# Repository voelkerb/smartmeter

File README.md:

# SmartMeter

The SmartMeter is a WiFi and Ethernet equipped electricity meter that to be installed in a home's fuse box. 
The development started with hardware [Version 1.0](/Schematic/Version_1). It consists of an ESP32 microcontroller and a dedicated electricity monitoring chip. As the main idea behind this project was to record voltage and current waveforms at higher frequencies, several drawbacks for this use case were fixed with Hardware [Version 2.0](/Schematic/Version_2). It features the same Microcontroller but with 8MB internal storage for data buffering, an RTC for precise time keeping while sampling, a faster USB serial connection with up to 12Mbaud and a 100Mbit ethernet interface.

If you are just interested in the consumption of a single appliance, see the [PowerMeter](https://github.com/voelkerb/powermeter) instead.

## Why to use?
It's open source, easy to use, easy to build and offers lots of flexibility. 

The hardware is...
* tested to work reliable with 230V.
* rather cheap (all components sum up to around 70€).

The firmware supports...
* existing 2.4GHz WPA2 networks or can create its own network.
* to receive commands via USB, TCP or MQTT.
* to store the configuration in the internal non volatile memory.
* to provide data at sampling rates from 1/5Hz all the way up to 32kHz.
* to calibrate the measurements.
* integration into most existing smart home systems e.g. HomeKit (via homebridge and MQTT).
* FFMpeg streaming. This allows to store high frequency data directly into files (e.g. MKV).

## How to build one?
You want to build your own SmartMeter? As the PCBs are provided in this repo, you can simply make your own.

Depending on your requirements, you might either build [Version 1.0](/Schematic/Version_1) or [Version 2.0](/Schematic/Version_2). 
* [Version 1.0](/Schematic/Version_1)
    * Benefits: 
        * The parts are cheaper (around 50€).
    * Drawbacks:
        * Cannot stream data of more than 8kHz.
        * No ethernet interface.
* [Version 2.0](/Schematic/Version_2)
    * Benefits: 
        * 8MB of internal storage allows to buffer data. If you stream high frequency data at e.g. 2kHz, this can hold up to 200s of data on network dropouts.
        * An RTC keeps track of time allowing you to synchronize sampling rates during high frequency sampling.
    * Drawbacks:
        * A little bit more expensive (parts around 70€).

Steps to build your own SmartMeter:
1. Make the PCB ([Version 1.0](/Schematic/Version_1) or [Version 2.0](/Schematic/Version_2)) with [SampleBoard](/Schematic/SampleBoard)). I recommend to use [JLC](https://jlcpcb.com) as it is super cheap and the quality is still decent.
2. Buy the parts listed under [BOM](/BOM).
3. Solder everything together. We used a small reflow oven, but it could also be done using a fine soldering iron. 
4. Buy a matching housing. We highly recommend to use [this one](https://www.voelkner.de/products/694730/Weltron-MR9-C-FA-RAL7035-ABS-Hutschienen-Gehaeuse-157.5-x-90-x-68-ABS-Lichtgrau-RAL-7035-1St..html) as the PCB was specially designed for it, the mounting holes match, and it is safe to use with 230V. It further can be installed inside fuse boxes at regular DIN rails. Also see the CAM milling files to generate cutouts for USB and ethernet and mounting plates for the sampler board (see [Housing](/Hosuing)). 
5. Install the SmartMeter at the DIN rail inside fuse box (that should be done by an electrician).

6. Wire the SmartMeter using the following diagram. 

7. Upload the [firmware](/Firmware) according to the instructions for your version. 
8. Interface with the SmartMeter accordingly as stated [here](/docu/README_Firmware_Cmds.md) 

# Use cases
## Smart homes
There are plenty of use cases for a smart plug inside a smart home.
* Get the power consumption of your home using a voice assistant or your smartphone
* Include it in home automation software to switch appliances based on an automation. There are lots of possibilities here, e.g.: 
    * Trigger an alert if the consumption exceeds a limit.

* Implement your own Non-Intrusive Load Monitoring System to get the individual appliance power consumption without adding smart plugs to each and every appliance.
* Monitor the power consumption of your home over day.

## For research purpose
* Analyze high frequency voltage and current waveforms.
* Record high frequency electricity datasets (see e.g. the [FIRED](https://github.com/voelkerb/FIRED_dataset_helper) dataset which can be used for Non-Intrusive Load Monitoring).

# License:
## Firmware:
Copyright (c) 2019 Benjamin Völker. All rights reserved.
This work is licensed under the terms of the [CC 4.0 licence](https://creativecommons.org/licenses/by/4.0/).

## Hardware:
Copyright (c) 2019 Benjamin Völker. All rights reserved.
This work is licensed under the terms of the [TAPR Open Hardware License](https://web.tapr.org/TAPR_Open_Hardware_License_v1.0.txt).

# Reference

Please cite our publications if you compare to or use this system:
* Benjamin Völker, Philipp M. Scholl, and Bernd Becker. 2019. Semi-Automatic Generation and Labeling of Training Data for Non-intrusive Load Monitoring. In Proceedings of the Tenth ACM International Conference on Future Energy Systems (e-Energy '19). Association for Computing Machinery, New York, NY, USA, 17–23. DOI:https://doi.org/10.1145/3307772.3328295
 
* Benjamin Völker, Marc Pfeifer, Philipp M. Scholl, and Bernd Becker. 2020. FIRED: A Fully-labeled hIgh-fRequency Electricity Disaggregation Dataset. In Proceedings of the 7th ACM International Conference on Systems for Energy-Efficient Buildings, Cities, and Transportation (BuildSys '20). Association for Computing Machinery, New York, NY, USA, 294–297. DOI:https://doi.org/10.1145/3408308.3427623

* Völker, B.; Pfeifer, M.; Scholl, P.M.; Becker, B. A Framework to Generate and Label Datasets for Non-Intrusive Load Monitoring. Energies 2021, 14, 75. https://doi.org/10.3390/en14010075

Kudos also go to Gregor Richter for developing the first draft schematics prior to [Version 1.0](/Schematic/Version_1).

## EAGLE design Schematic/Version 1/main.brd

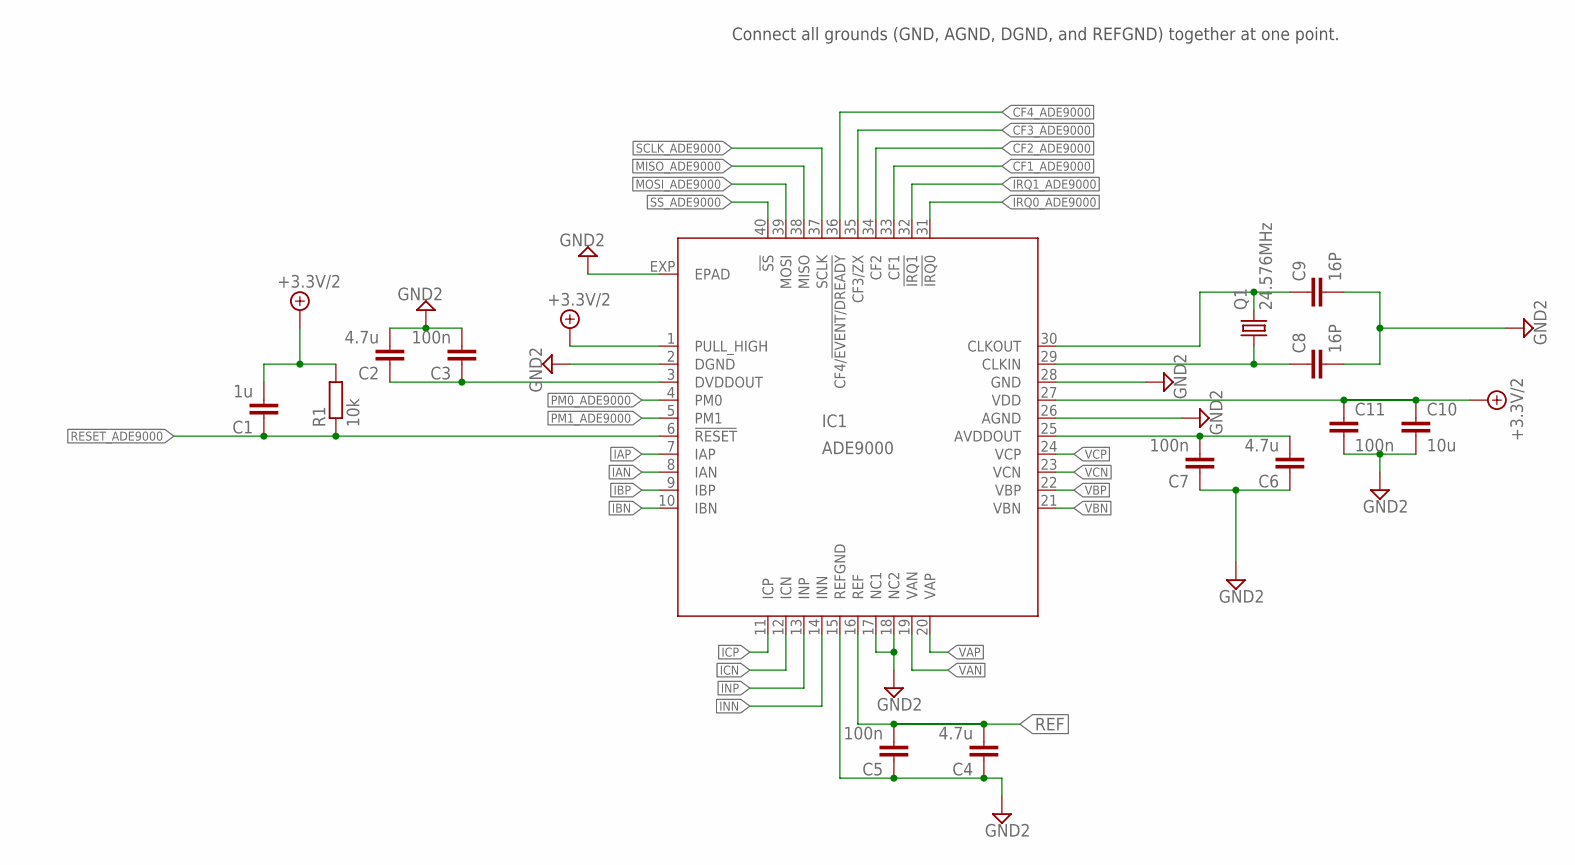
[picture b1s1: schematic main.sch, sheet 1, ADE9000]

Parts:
C1: 1u; C0805
C2, C4, C6: 4.7u; C0805
C3, C5, C7, C11: 100n; C0805
C8, C9: 16P; C0805K
C10: 10u; C1206K
IC1: ADE9000; QFN40
Q1: 24.576MHz; HC49UP
R1: 10k; R0805

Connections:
!IRQ0!_ADE9000: IC1.31 (!IRQ0); also elsewhere on the board
!IRQ1!_ADE9000: IC1.32 (!IRQ1); also elsewhere on the board
!RESET!_ADE9000: C1.1, IC1.6 (!RESET), R1.1; also elsewhere on the board
+3.3V/2: C1.2, C10.1, C11.1, IC1.1 (PULL_HIGH), IC1.27 (VDD), R1.2; also elsewhere on the board
CF1_ADE9000: IC1.33 (CF1); also elsewhere on the board
CF2_ADE9000: IC1.34 (CF2); also elsewhere on the board
CF3_ADE9000: IC1.35 (CF3/ZX); also elsewhere on the board
CF4_ADE9000: IC1.36 (CF4/!EVENT/DREADY); also elsewhere on the board
GND2: C2.2, C3.2, C4.1, C5.1, C6.1, C7.1, C8.2, C9.2, C10.2, C11.2, IC1.2 (DGND), IC1.15 (REFGND), IC1.17 (NC1), IC1.18 (NC2), IC1.26 (AGND), IC1.28 (GND), IC1.EXP (EPAD); also elsewhere on the board
IAN: IC1.8 (IAN); also elsewhere on the board
IAP: IC1.7 (IAP); also elsewhere on the board
IBN: IC1.10 (IBN); also elsewhere on the board
IBP: IC1.9 (IBP); also elsewhere on the board
ICN: IC1.12 (ICN); also elsewhere on the board
ICP: IC1.11 (ICP); also elsewhere on the board
INN: IC1.14 (INN); also elsewhere on the board
INP: IC1.13 (INP); also elsewhere on the board
MISO_ADE9000: IC1.38 (MISO); also elsewhere on the board
MOSI_ADE9000: IC1.39 (MOSI); also elsewhere on the board
unnamed: C2.1, C3.1, IC1.3 (DVDDOUT)
unnamed: C6.2, C7.2, IC1.25 (AVDDOUT)
unnamed: C8.1, IC1.29 (CLKIN), Q1.1
unnamed: C9.1, IC1.30 (CLKOUT), Q1.2
PM0_ADE9000: IC1.4 (PM0); also elsewhere on the board
PM1_ADE9000: IC1.5 (PM1); also elsewhere on the board
REF: C4.2, C5.2, IC1.16 (REF); also elsewhere on the board
SCLK_ADE9000: IC1.37 (SCLK); also elsewhere on the board
SS_ADE9000: IC1.40 (!SS); also elsewhere on the board
VAN: IC1.19 (VAN); also elsewhere on the board
VAP: IC1.20 (VAP); also elsewhere on the board
VBN: IC1.21 (VBN); also elsewhere on the board
VBP: IC1.22 (VBP); also elsewhere on the board
VCN: IC1.23 (VCN); also elsewhere on the board
VCP: IC1.24 (VCP); also elsewhere on the board

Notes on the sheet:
Connect all grounds (GND, AGND, DGND, and REFGND) together at one point.

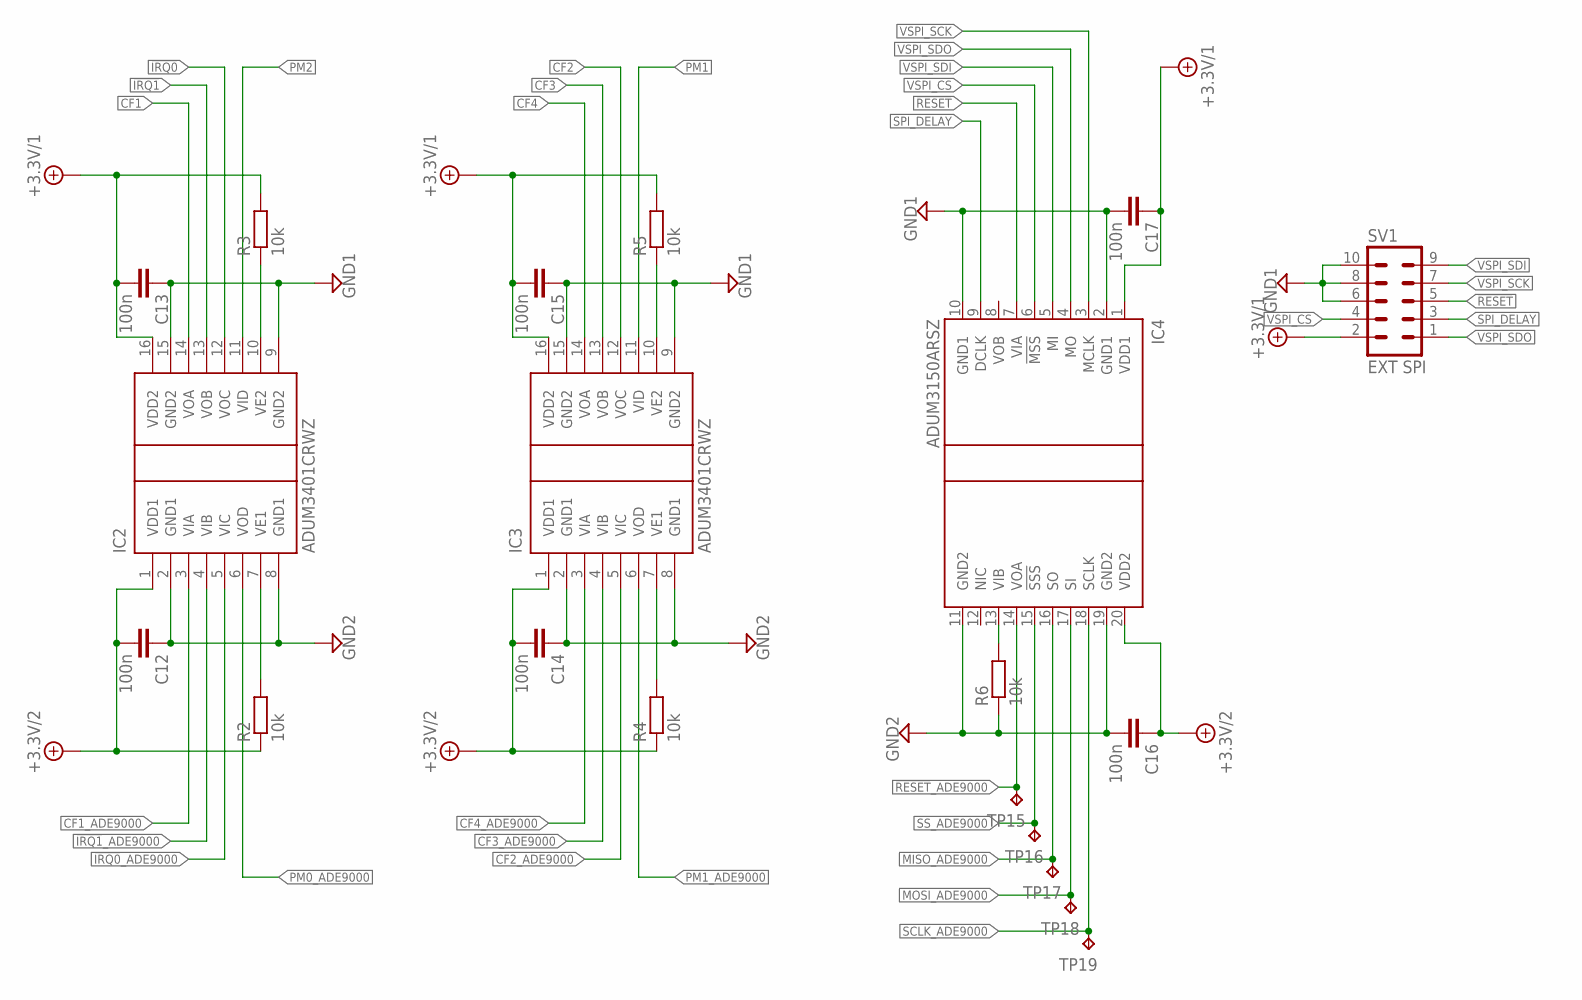
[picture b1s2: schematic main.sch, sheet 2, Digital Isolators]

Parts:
C12, C13, C14, C15, C16, C17: 100n; C0805
IC2, IC3: ADUM3401CRWZ; SO16W
IC4: ADUM3150ARSZ; SSOP20
R2, R3, R4, R5, R6: 10k; R0805
SV1: EXT SPI; ML10
TP15, TP16, TP17, TP18, TP19: TPB1,27; B1,27

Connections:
!IRQ0: IC2.12 (VOC); also elsewhere on the board
!IRQ0!_ADE9000: IC2.5 (VIC); also elsewhere on the board
!IRQ1: IC2.13 (VOB); also elsewhere on the board
!IRQ1!_ADE9000: IC2.4 (VIB); also elsewhere on the board
!RESET: IC4.7 (VIA), SV1.5; also elsewhere on the board
!RESET!_ADE9000: IC4.14 (VOA), TP15.TP; also elsewhere on the board
+3.3V/1: C13.2, C15.2, C17.1, IC2.16 (VDD2), IC3.16 (VDD2), IC4.1 (VDD1), R3.2, R5.2, SV1.2; also elsewhere on the board
+3.3V/2: C12.2, C14.2, C16.1, IC2.1 (VDD1), IC3.1 (VDD1), IC4.20 (VDD2), R2.1, R4.1; also elsewhere on the board
CF1: IC2.14 (VOA); also elsewhere on the board
CF1_ADE9000: IC2.3 (VIA); also elsewhere on the board
CF2: IC3.12 (VOC); also elsewhere on the board
CF2_ADE9000: IC3.5 (VIC); also elsewhere on the board
CF3: IC3.13 (VOB); also elsewhere on the board
CF3_ADE9000: IC3.4 (VIB); also elsewhere on the board
CF4: IC3.14 (VOA); also elsewhere on the board
CF4_ADE9000: IC3.3 (VIA); also elsewhere on the board
GND1: C13.1, C15.1, C17.2, IC2.9 (GND2), IC2.15 (GND2), IC3.9 (GND2), IC3.15 (GND2), IC4.2 (GND1), IC4.10 (GND1), SV1.6, SV1.8, SV1.10; also elsewhere on the board
GND2: C12.1, C14.1, C16.2, IC2.2 (GND1), IC2.8 (GND1), IC3.2 (GND1), IC3.8 (GND1), IC4.11 (GND2), IC4.19 (GND2), R6.1; also elsewhere on the board
MISO_ADE9000: IC4.16 (SO), TP17.TP; also elsewhere on the board
MOSI_ADE9000: IC4.17 (SI), TP18.TP; also elsewhere on the board
unnamed: IC2.10 (VE2), R3.1
unnamed: IC4.13 (VIB), R6.2
unnamed: IC3.7 (VE1), R4.2
unnamed: IC3.10 (VE2), R5.1
unnamed: IC2.7 (VE1), R2.2
PM0_ADE9000: IC2.6 (VOD); also elsewhere on the board
PM1: IC3.11 (VID); also elsewhere on the board
PM1_ADE9000: IC3.6 (VOD); also elsewhere on the board
PM2: IC2.11 (VID); also elsewhere on the board
SCLK_ADE9000: IC4.18 (SCLK), TP19.TP; also elsewhere on the board
SPI_DELAY: IC4.9 (DCLK), SV1.3; also elsewhere on the board
SS_ADE9000: IC4.15 (!SSS), TP16.TP; also elsewhere on the board
VSPI_CS: IC4.6 (!MSS), SV1.4; also elsewhere on the board
VSPI_SCK: IC4.3 (MCLK), SV1.7; also elsewhere on the board
VSPI_SDI: IC4.5 (MI), SV1.9; also elsewhere on the board
VSPI_SDO: IC4.4 (MO), SV1.1; also elsewhere on the board

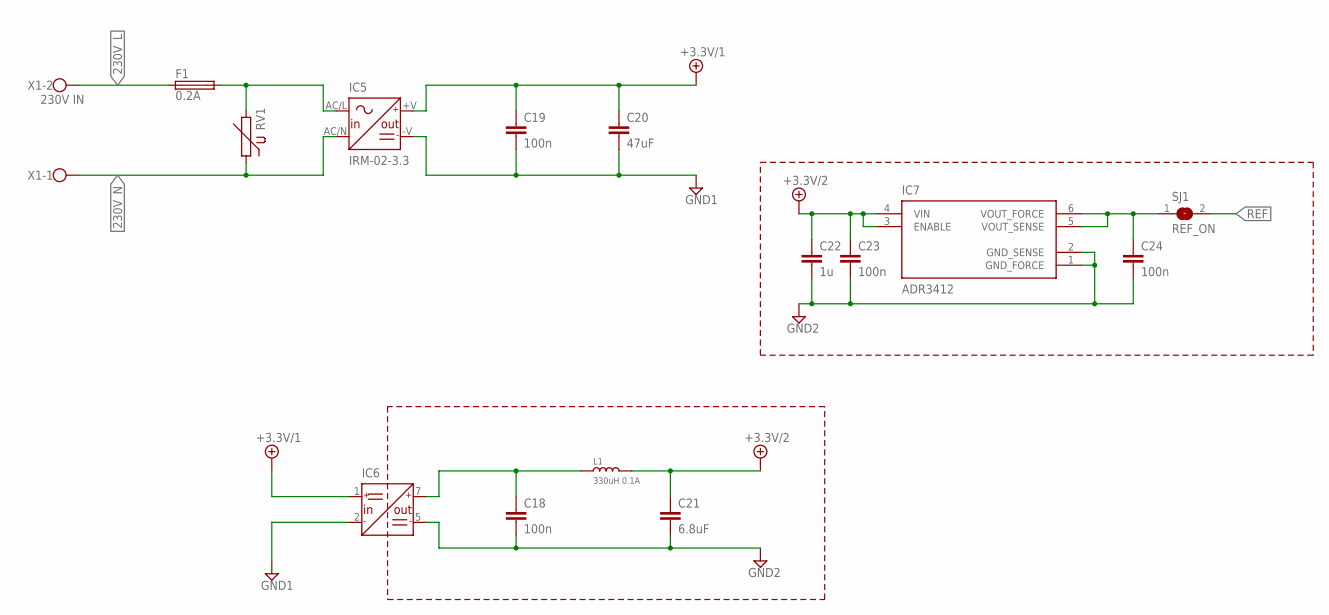
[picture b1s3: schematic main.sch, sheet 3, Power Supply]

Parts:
C18, C19, C23, C24: 100n; C0805
C20: 47uF; C3216
C21: 6.8uF; C3216
C22: 1u; C0805
F1: 0.2A; SH22,5A
IC5: IRM-02-3.3; MW_IRM-02
IC6: MURATA-PS-MEF1SXXXXSP3C; SIP-7PIN-1257
IC7: ADR3412; SOT-23-6
L1: 330uH 0.1A; L1008
RV1: B72210S0321K101; TDK_E7.5_A2.4_W12.0_TH5.4_H15.0_D0.8
SJ1: REF_ON; SJ
X1: 230V IN; W237-113

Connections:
230V_L: F1.1, X1.2
230V_N: IC5.AC/N (N), RV1.1, X1.1
+3.3V/1: C19.1, C20.1, IC5.+V (+V_OUT), IC6.1 (+V_IN); also elsewhere on the board
+3.3V/2: C21.1, C22.1, C23.1, IC7.3 (ENABLE), IC7.4 (VIN), L1.2; also elsewhere on the board
GND1: C19.2, C20.2, IC5.-V (-V_OUT), IC6.2 (-V_IN); also elsewhere on the board
GND2: C18.2, C21.2, C22.2, C23.2, C24.2, IC6.5 (-V_OUT), IC7.1 (GND_FORCE), IC7.2 (GND_SENSE); also elsewhere on the board
unnamed: C18.1, IC6.7 (+V_OUT), L1.1
unnamed: F1.2, IC5.AC/L (L), RV1.2
unnamed: C24.1, IC7.5 (VOUT_SENSE), IC7.6 (VOUT_FORCE), SJ1.1
REF: SJ1.2; also elsewhere on the board

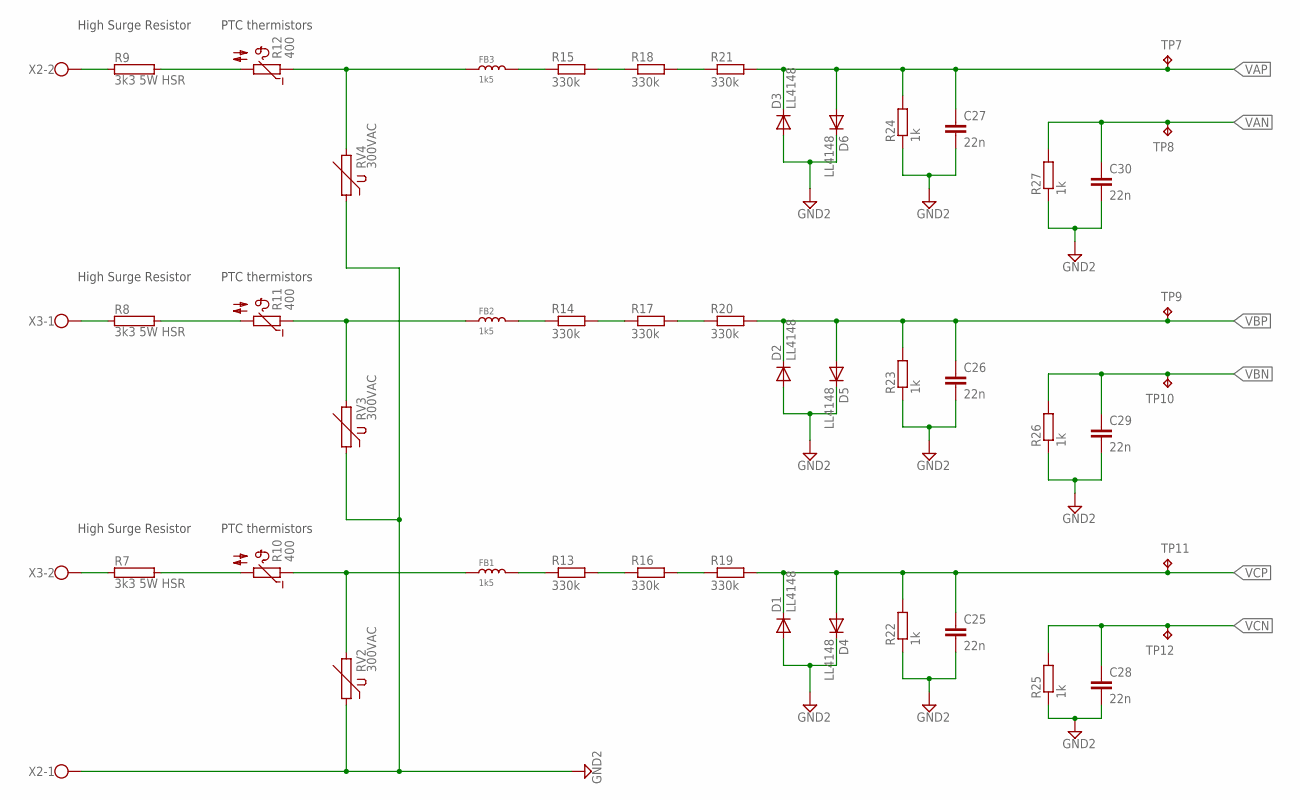
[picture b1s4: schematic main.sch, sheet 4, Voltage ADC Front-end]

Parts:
C25, C26, C27, C28, C29, C30: 22n; C0805
D1, D2, D3, D4, D5, D6: LL4148; SOD80C
FB1, FB2, FB3: 1k5; L0805
R7, R8, R9: 3k3 5W HSR; AC05
R10, R11, R12: 400; PTCCL10H010SBE
R13, R14, R15, R16, R17, R18, R19, R20, R21: 330k; R1206
R22, R23, R24, R25, R26, R27: 1k; R1206
RV2, RV3, RV4: 300VAC; TDK_E10.0_A2.4_W21.5_TH5.6_H25.5_D1.0
TP7, TP8, TP9, TP10, TP11, TP12: TPB1,27; B1,27
X2, X3: W237-113

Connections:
GND2: C25.2, C26.2, C27.2, C28.2, C29.2, C30.2, D1.A, D2.A, D3.A, D4.C, D5.C, D6.C, R22.1, R23.1, R24.1, R25.1, R26.1, R27.1, RV2.1, RV3.1, RV4.1, X2.1; also elsewhere on the board
unnamed: R9.2, R12.2
unnamed: FB3.1, R12.1, RV4.2
unnamed: FB3.2, R15.1
unnamed: R8.2, R11.2
unnamed: FB2.1, R11.1, RV3.2
unnamed: R7.1, X3.2
unnamed: R15.2, R18.1
unnamed: FB2.2, R14.1
unnamed: R14.2, R17.1
unnamed: R17.2, R20.1
unnamed: R18.2, R21.1
unnamed: R7.2, R10.2
unnamed: FB1.1, R10.1, RV2.2
unnamed: R8.1, X3.1
unnamed: FB1.2, R13.1
unnamed: R13.2, R16.1
unnamed: R16.2, R19.1
unnamed: R9.1, X2.2
VAN: C30.1, R27.2, TP8.TP; also elsewhere on the board
VAP: C27.1, D3.C, D6.A, R21.2, R24.2, TP7.TP; also elsewhere on the board
VBN: C29.1, R26.2, TP10.TP; also elsewhere on the board
VBP: C26.1, D2.C, D5.A, R20.2, R23.2, TP9.TP; also elsewhere on the board
VCN: C28.1, R25.2, TP12.TP; also elsewhere on the board
VCP: C25.1, D1.C, D4.A, R19.2, R22.2, TP11.TP; also elsewhere on the board

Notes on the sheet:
High Surge Resistor
PTC thermistors

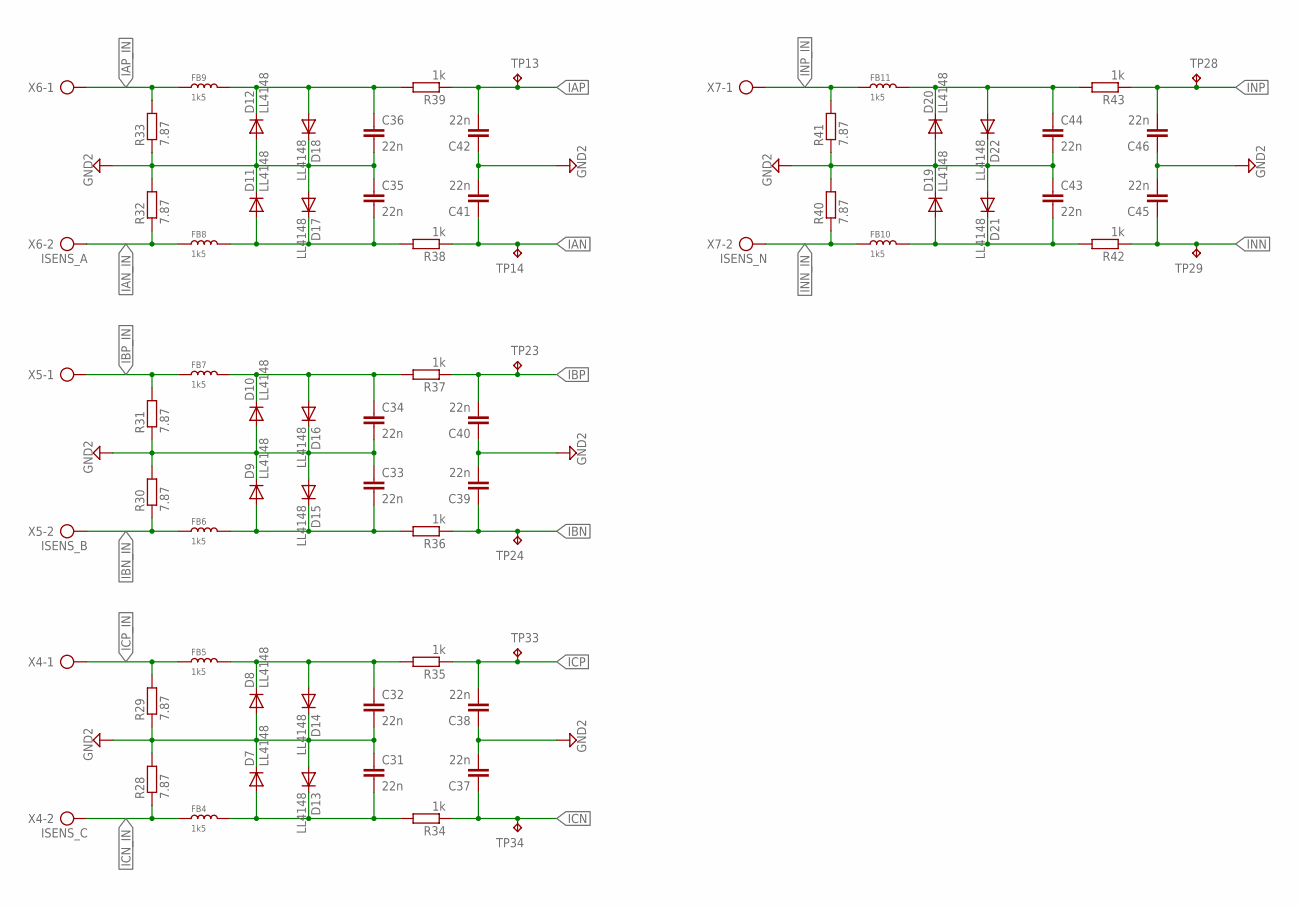
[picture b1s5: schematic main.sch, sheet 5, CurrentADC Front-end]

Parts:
C31, C32, C33, C34, C35, C36, C37, C38, C39, C40, C41, C42, C43, C44, C45, C46: 22n; C0805
D7, D8, D9, D10, D11, D12, D13, D14, D15, D16, D17, D18, D19, D20, D21, D22: LL4148; SOD80C
FB4, FB5, FB6, FB7, FB8, FB9, FB10, FB11: 1k5; L0805
R28, R29, R30, R31, R32, R33, R40, R41: 7.87; R1206
R34, R35, R36, R37, R38, R39, R42, R43: 1k; R1206
TP13, TP14, TP23, TP24, TP28, TP29, TP33, TP34: TPB1,27; B1,27
X4: ISENS_C; AK500/2
X5: ISENS_B; AK500/2
X6: ISENS_A; AK500/2
X7: ISENS_N; AK500/2

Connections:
GND2: C31.1, C32.2, C33.1, C34.2, C35.1, C36.2, C37.2, C38.1, C39.2, C40.1, C41.2, C42.1, C43.1, C44.2, C45.2, C46.1, D7.C, D8.A, D9.C, D10.A, D11.C, D12.A, D13.A, D14.C, D15.A, D16.C, D17.A, D18.C, D19.C, D20.A, D21.A, D22.C, R28.2, R29.1, R30.2, R31.1, R32.2, R33.1, R40.2, R41.1; also elsewhere on the board
IAN: C41.1, R38.1, TP14.TP; also elsewhere on the board
IAN_IN: FB8.1, R32.1, X6.2
IAP: C42.2, R39.1, TP13.TP; also elsewhere on the board
IAP_IN: FB9.1, R33.2, X6.1
IBN: C39.1, R36.1, TP24.TP; also elsewhere on the board
IBN_IN: FB6.1, R30.1, X5.2
IBP: C40.2, R37.1, TP23.TP; also elsewhere on the board
IBP_IN: FB7.1, R31.2, X5.1
ICN: C37.1, R34.1, TP34.TP; also elsewhere on the board
ICN_IN: FB4.1, R28.1, X4.2
ICP: C38.2, R35.1, TP33.TP; also elsewhere on the board
ICP_IN: FB5.1, R29.2, X4.1
INN: C45.1, R42.1, TP29.TP; also elsewhere on the board
INN_IN: FB10.1, R40.1, X7.2
INP: C46.2, R43.1, TP28.TP; also elsewhere on the board
INP_IN: FB11.1, R41.2, X7.1
unnamed: C33.2, D9.A, D15.C, FB6.2, R36.2
unnamed: C43.2, D19.A, D21.C, FB10.2, R42.2
unnamed: C31.2, D7.A, D13.C, FB4.2, R34.2
unnamed: C35.2, D11.A, D17.C, FB8.2, R38.2
VBN1: C36.1, D12.C, D18.A, FB9.2, R39.2
VBN2: C34.1, D10.C, D16.A, FB7.2, R37.2
VBN3: C44.1, D20.C, D22.A, FB11.2, R43.2
VBN4: C32.1, D8.C, D14.A, FB5.2, R35.2

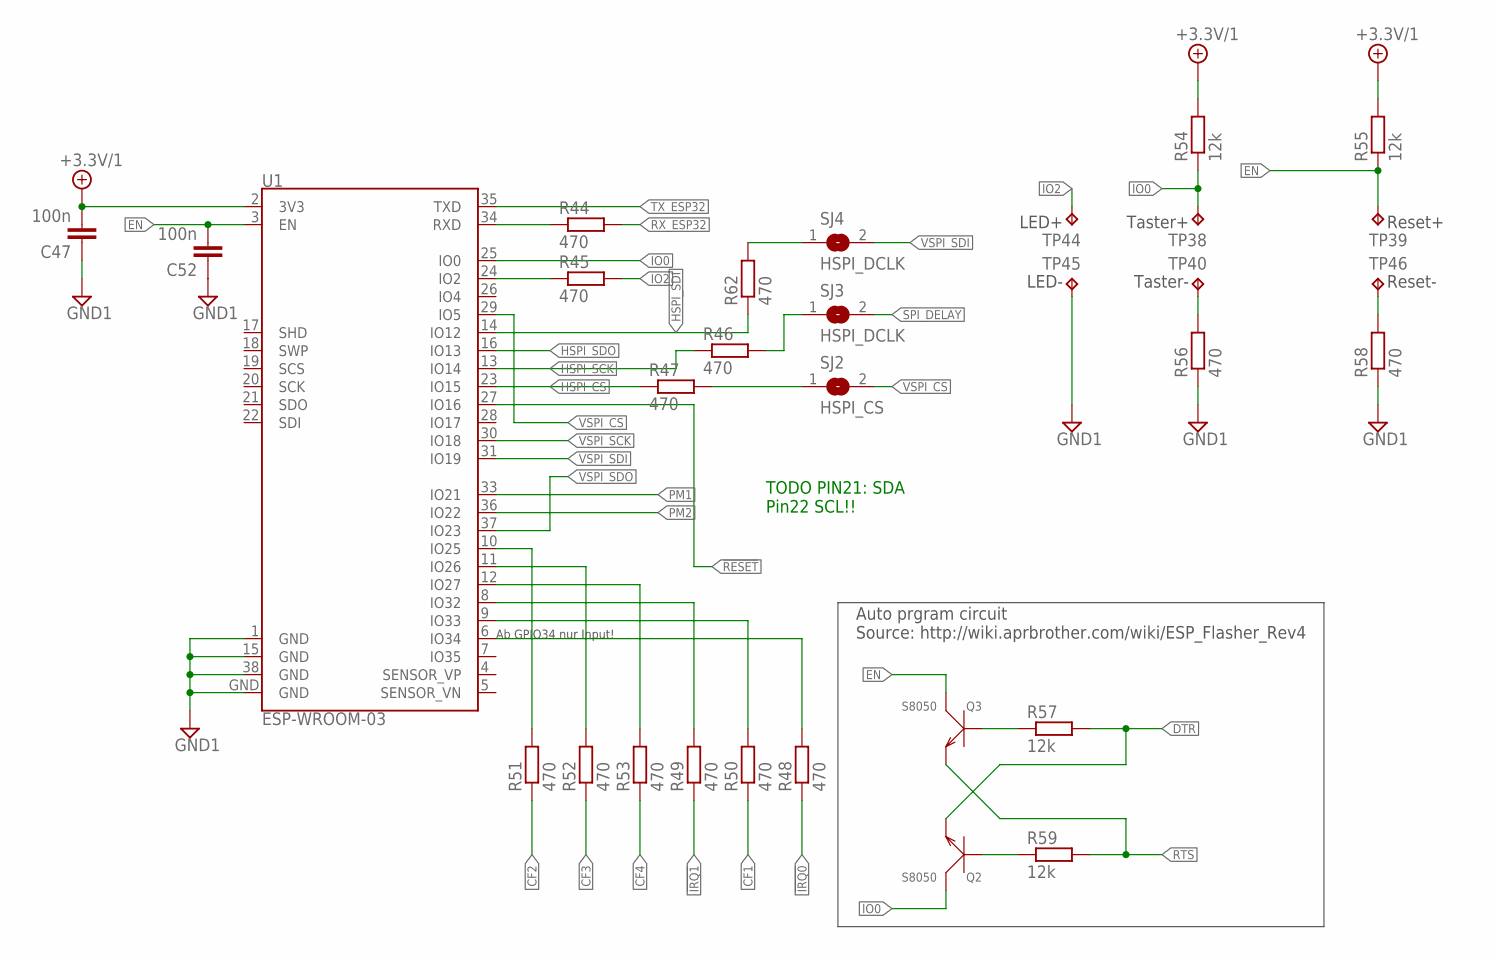
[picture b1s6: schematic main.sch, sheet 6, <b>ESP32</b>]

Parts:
C47, C52: 100n; C0805
Q2, Q3: S8050; SOT-23
R44, R45, R46, R47, R48, R49, R50, R51, R52, R53, R56, R58, R62: 470; R0805
R54, R55, R57, R59: 12k; R0805
SJ2: HSPI_CS; SJ
SJ3, SJ4: HSPI_DCLK; SJ
TP38, TP39, TP40, TP44, TP45, TP46: TPPAD1-13Y; P1-13Y
U1: ESP-WROOM-03

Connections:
!IRQ0: R48.1; also elsewhere on the board
!IRQ1: R49.1; also elsewhere on the board
!RESET: U1.27 (IO16); also elsewhere on the board
+3.3V/1: C47.2, R54.2, R55.2, U1.2 (3V3); also elsewhere on the board
CF1: R50.1; also elsewhere on the board
CF2: R51.1; also elsewhere on the board
CF3: R52.1; also elsewhere on the board
CF4: R53.1; also elsewhere on the board
DTR: Q2.2 (E), R57.2; also elsewhere on the board
EN: C52.2, Q3.3 (C), R55.1, TP39.TP, U1.3 (EN)
GND1: C47.1, C52.1, R56.1, R58.1, TP45.TP, U1.1 (GND), U1.15 (GND), U1.38 (GND), U1.GND; also elsewhere on the board
HSPI_CS: R47.1, U1.23 (IO15)
HSPI_SCK: R46.1, U1.13 (IO14)
HSPI_SDI: R62.1, U1.14 (IO12)
HSPI_SDO: U1.16 (IO13)
IO0: Q2.3 (C), R54.1, TP38.TP, U1.25 (IO0)
IO2: R45.2, TP44.TP
unnamed: R62.2, SJ4.1
unnamed: R44.1, U1.34 (RXD)
unnamed: R45.1, U1.24 (IO2)
unnamed: Q3.1 (B), R57.1
unnamed: Q2.1 (B), R59.1
unnamed: R56.2, TP40.TP
unnamed: R58.2, TP46.TP
unnamed: R46.2, SJ3.1
unnamed: R47.2, SJ2.1
unnamed: R48.2, U1.6 (IO34)
unnamed: R49.2, U1.8 (IO32)
unnamed: R50.2, U1.9 (IO33)
unnamed: R51.2, U1.10 (IO25)
unnamed: R52.2, U1.11 (IO26)
unnamed: R53.2, U1.12 (IO27)
PM1: U1.33 (IO21); also elsewhere on the board
PM2: U1.36 (IO22); also elsewhere on the board
RTS: Q3.2 (E), R59.2; also elsewhere on the board
RX_ESP32: R44.2; also elsewhere on the board
SPI_DELAY: SJ3.2; also elsewhere on the board
TX_ESP32: U1.35 (TXD); also elsewhere on the board
VSPI_CS: SJ2.2, U1.29 (IO5); also elsewhere on the board
VSPI_SCK: U1.30 (IO18); also elsewhere on the board
VSPI_SDI: SJ4.2, U1.31 (IO19); also elsewhere on the board
VSPI_SDO: U1.37 (IO23); also elsewhere on the board

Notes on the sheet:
Ab GPIO34 nur Input!
TODO PIN21: SDA Pin22 SCL!!
Auto prgram circuit Source: http://wiki.aprbrother.com/wiki/ESP_Flasher_Rev4

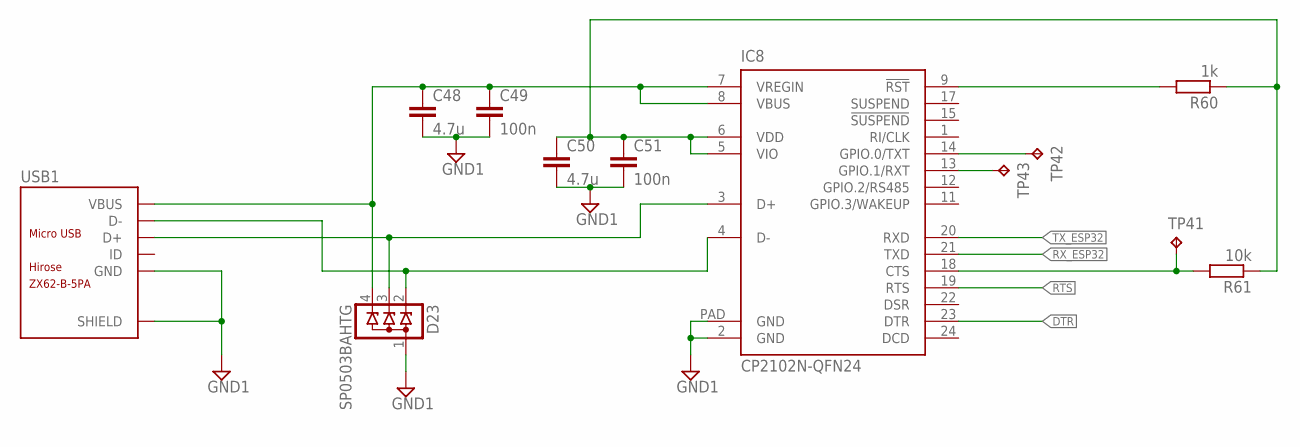
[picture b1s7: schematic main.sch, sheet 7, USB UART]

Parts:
C48, C50: 4.7u; C0805
C49, C51: 100n; C0805
D23: SP0503BAHTG; SOT143-4-R
IC8: CP2102N-QFN24; QFN24
R60: 1k; R0805
R61: 10k; R0805
TP41, TP42, TP43: TPB1,27; B1,27
USB1: ZX62-B-5PA; MICRO-USB5+6P-SMD-0.65-AB

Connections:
CP2102_3.3V: C50.1, C51.1, IC8.5 (VIO), IC8.6 (VDD), R60.1, R61.1
DTR: IC8.23 (DTR); also elsewhere on the board
GND1: C48.2, C49.2, C50.2, C51.2, D23.1, IC8.2 (GND), IC8.PAD (GND), USB1.5 (GND), USB1.P1 (SHIELD), USB1.P2 (SHIELD), USB1.P3 (SHIELD), USB1.P4 (SHIELD), USB1.P5 (SHIELD), USB1.P6 (SHIELD); also elsewhere on the board
unnamed: IC8.18 (CTS), R61.2, TP41.TP
unnamed: IC8.9 (!RST), R60.2
unnamed: IC8.14 (GPIO.0/TXT), TP42.TP
unnamed: IC8.13 (GPIO.1/RXT), TP43.TP
RTS: IC8.19 (RTS); also elsewhere on the board
RX_ESP32: IC8.21 (TXD); also elsewhere on the board
TX_ESP32: IC8.20 (RXD); also elsewhere on the board
USB_D+: D23.3, IC8.3 (D+), USB1.3 (D+)
USB_D-: D23.2, IC8.4 (D-), USB1.2 (D-)
VBUS: C48.1, C49.1, D23.4, IC8.7 (VREGIN), IC8.8 (VBUS), USB1.1 (VBUS)

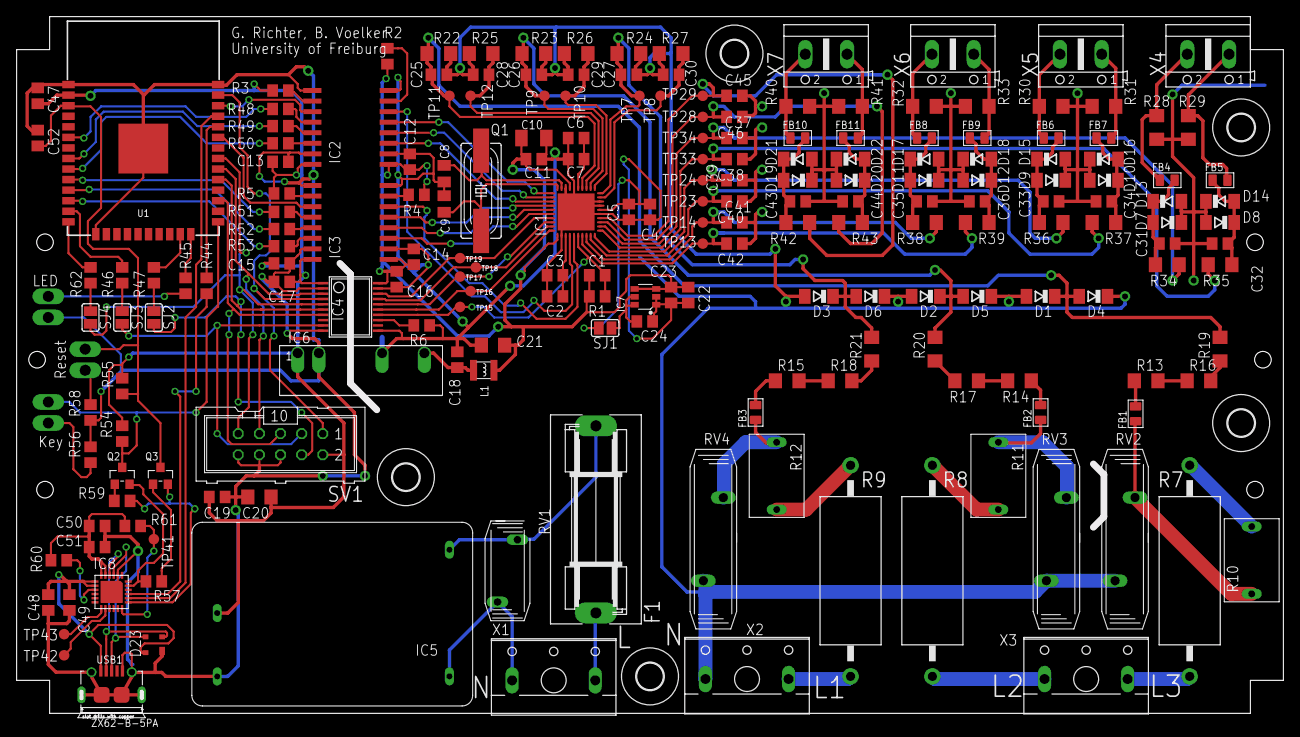
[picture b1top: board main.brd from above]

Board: 2 copper layers, 151.6 x 83.8 mm, 212 parts (0 on the bottom side), 127 nets.

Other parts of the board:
U$1, U$2, U$3, U$4, U$5: 3,2

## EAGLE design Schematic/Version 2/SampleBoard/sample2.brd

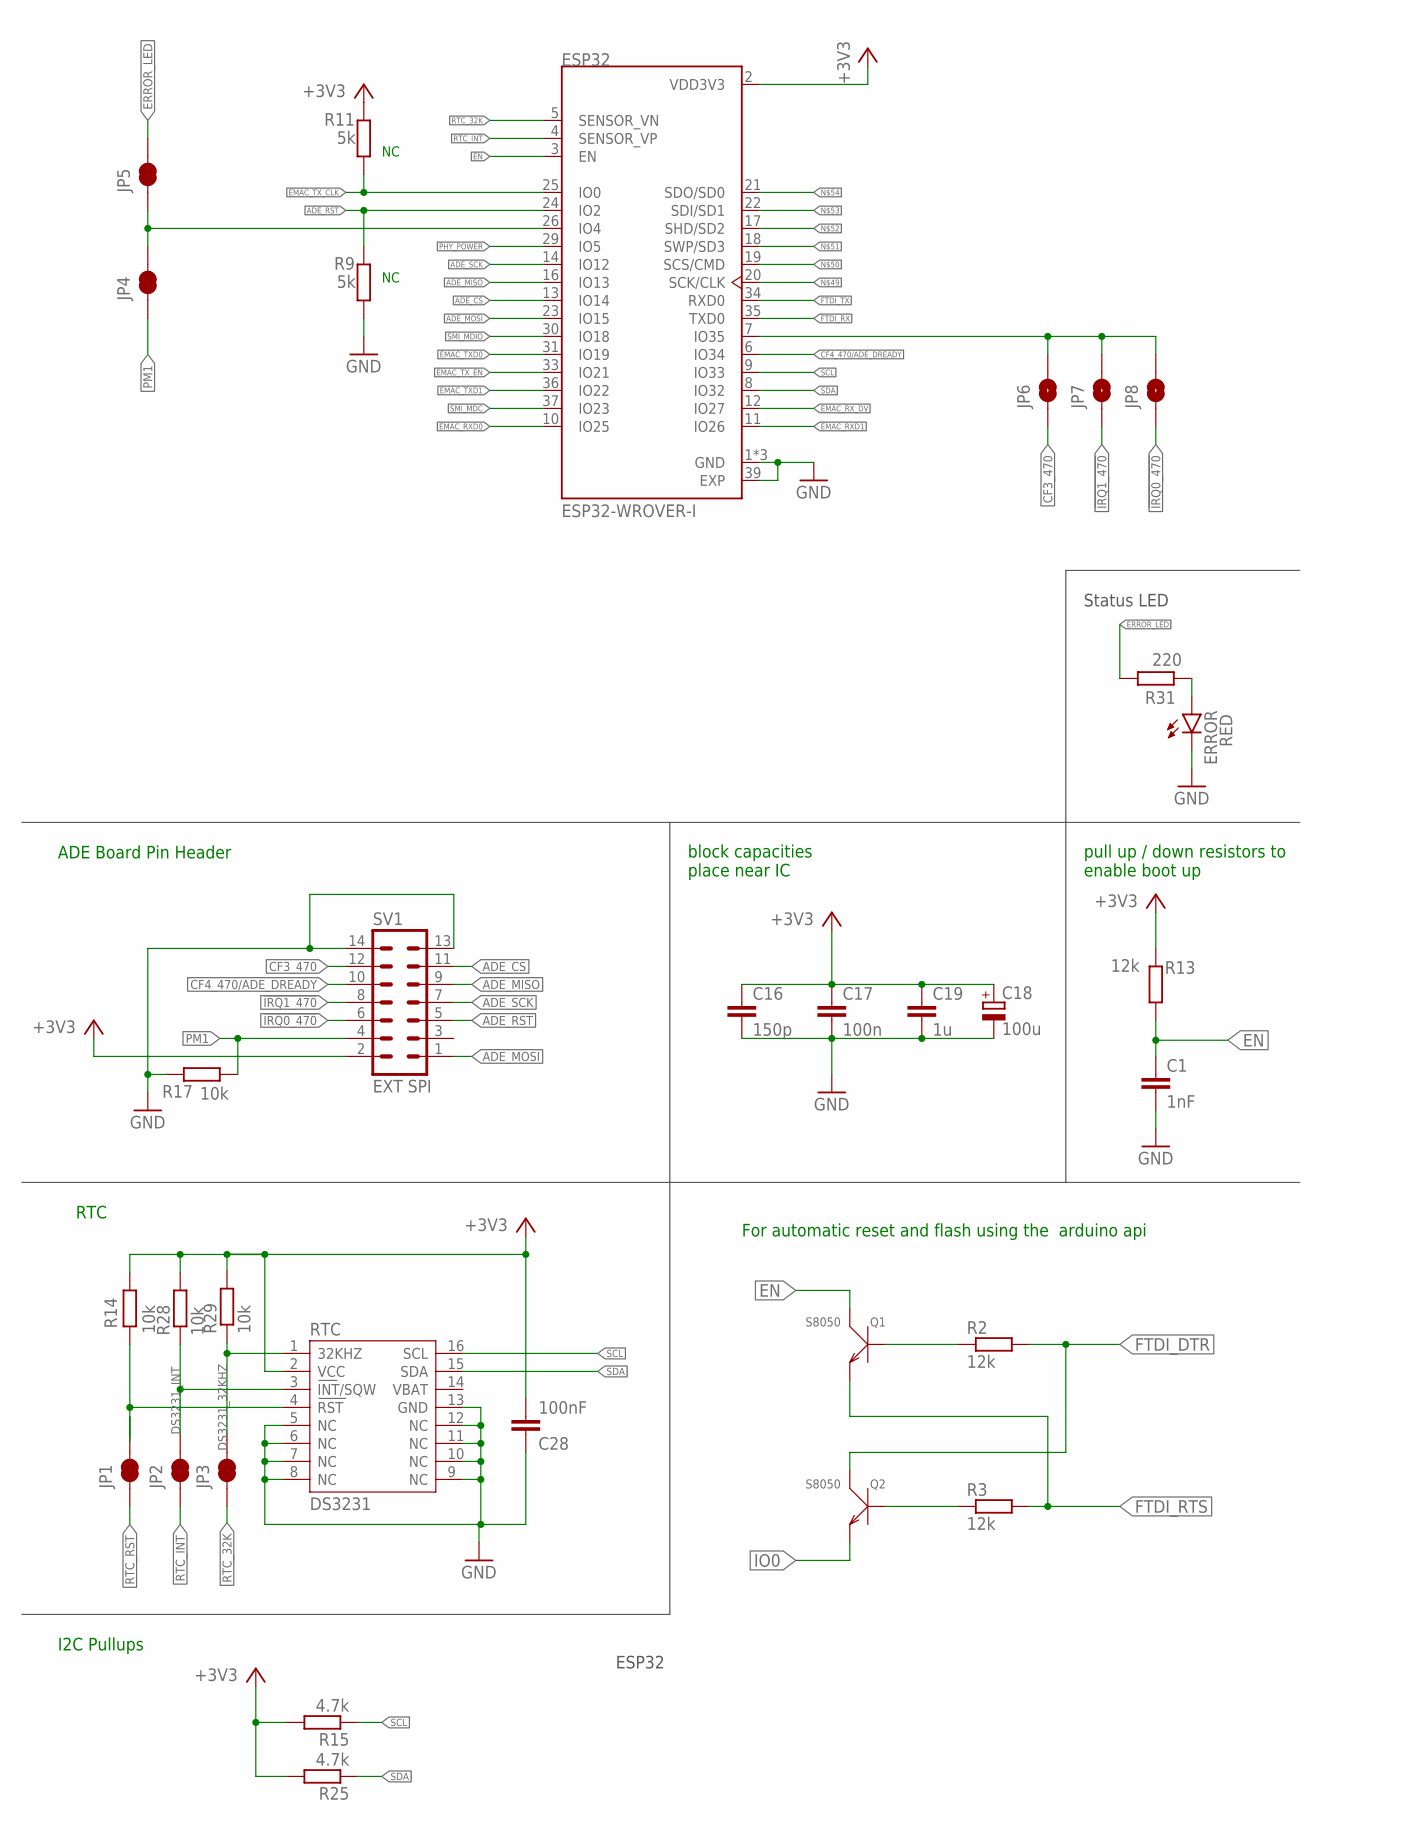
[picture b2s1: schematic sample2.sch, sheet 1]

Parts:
C1: 1nF; C0402
C16: 150p; C0402
C17: 100n; C0603
C18: 100u; D/7343-31W
C19: 1u; C0603
C28: 100nF; C0402
ERROR: RED; CHIP-LED0805
ESP32: ESP32-WROVER-I; XCVR_ESP32-WROVER-I
JP1, JP2, JP3, JP4, JP5: JUMPER-SMT_2_NC_TRACE_NO-SILK; SMT-JUMPER_2_NC_TRACE_NO-SILK
JP6, JP7, JP8: JUMPER-SMT_2_NO_NO-SILK; SMT-JUMPER_2_NO_NO-SILK
Q1, Q2: S8050; SOT-23
R2, R3, R13: 12k; R0402
R9, R11: 5k; R0402
R14, R28, R29: 10k; R0603
R15, R25: 4.7k; R0603
R17: 10k; R0402
R31: 220; R0603
RTC: DS3231
SV1: EXT SPI; ML14

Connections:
!IRQ0_470: JP8.2, SV1.6
!IRQ1_470: JP7.2, SV1.8
+3V3: C16.1, C17.1, C18.+, C19.1, C28.2, ESP32.2 (VDD3V3), R11.1, R13.1, R14.1, R15.2, R25.2, R28.2, R29.2, RTC.2 (VCC), SV1.2; also elsewhere on the board
ADE_CS: ESP32.13 (IO14), SV1.11
ADE_MISO: ESP32.16 (IO13), SV1.9
ADE_MOSI: ESP32.23 (IO15), SV1.1
ADE_RST: ESP32.24 (IO2), R9.2, SV1.5
ADE_SCK: ESP32.14 (IO12), SV1.7
CF3_470: JP6.1, SV1.12
CF4_470/ADE_DREADY: ESP32.6 (IO34), SV1.10
DS3231_32KHZ: JP3.2, R29.1, RTC.1 (32KHZ)
DS3231_INT: JP2.2, R28.1, RTC.3 (INT/SQW)
DS3231_RST: JP1.2, R14.2, RTC.4 (RST)
EMAC_RXD0: ESP32.10 (IO25); also elsewhere on the board
EMAC_RXD1: ESP32.11 (IO26); also elsewhere on the board
EMAC_RX_DV: ESP32.12 (IO27); also elsewhere on the board
EMAC_TXD0: ESP32.31 (IO19); also elsewhere on the board
EMAC_TXD1: ESP32.36 (IO22); also elsewhere on the board
EMAC_TX_CLK: ESP32.25 (IO0), R11.2; also elsewhere on the board
EMAC_TX_EN: ESP32.33 (IO21); also elsewhere on the board
EN: C1.1, ESP32.3 (EN), Q1.3 (C), R13.2
ERROR_LED: JP5.2, R31.1
FTDI_DTR: Q2.3 (C), R2.2; also elsewhere on the board
FTDI_RTS: Q1.2 (E), R3.2; also elsewhere on the board
FTDI_RX: ESP32.35 (TXD0); also elsewhere on the board
FTDI_TX: ESP32.34 (RXD0); also elsewhere on the board
GND: C1.2, C16.2, C17.2, C18.-, C19.2, C28.1, ERROR.C, ESP32.1 (GND), ESP32.15 (GND), ESP32.38 (GND), ESP32.39 (EXP), R9.1, R17.2, RTC.5 (NC), RTC.6 (NC), RTC.7 (NC), RTC.8 (NC), RTC.9 (NC), RTC.10 (NC), RTC.11 (NC), RTC.12 (NC), RTC.13 (GND), SV1.13, SV1.14; also elsewhere on the board
IO0: Q2.2 (E)
unnamed: Q1.1 (B), R2.1
unnamed: Q2.1 (B), R3.1
unnamed: ESP32.26 (IO4), JP4.2, JP5.1
unnamed: ERROR.A, R31.2
unnamed: ESP32.7 (IO35), JP6.2, JP7.1, JP8.1
PHY_POWER: ESP32.29 (IO5); also elsewhere on the board
PM1: JP4.1, R17.1, SV1.4
RTC_32K: ESP32.5 (SENSOR_VN), JP3.1
RTC_INT: ESP32.4 (SENSOR_VP), JP2.1
RTC_RST: JP1.1
SCL: ESP32.9 (IO33), R15.1, RTC.16 (SCL)
SDA: ESP32.8 (IO32), R25.1, RTC.15 (SDA)
SMI_MDC: ESP32.37 (IO23); also elsewhere on the board
SMI_MDIO: ESP32.30 (IO18); also elsewhere on the board

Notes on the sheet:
pull up / down resistors to enable boot up
For automatic reset and flash using the arduino api
ESP32
block capacities place near IC
RTC
I2C Pullups
Status LED
ADE Board Pin Header

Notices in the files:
parts and their libraries:
microbuilder: This work is placed in the public domain, and may be freely used for commercial and non-commercial work with the following conditions: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
SparkFun-Connectors: Licensing: Creative Commons ShareAlike 4.0 International - https://creativecommons.org/licenses/by-sa/4.0
